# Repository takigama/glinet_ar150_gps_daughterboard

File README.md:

## Update - 2020, Mar 9

I've been running my little guys for 3 years now. I have two in outdoor cases
being powered over ethernet and they have yet to skip a beat, which is suprising.
As some of you may know, Australia (especially NSW) has been going through
some hard times this summer. First it was an amazing heatwave followed by fire
Then it was floods and intense rain. They endured both. Going up against two
RPI's (both RPI's died in the heat), thats doing pretty well.

I've now added a 2020 firmware release which is based on 19.07.2. This time
i've included all the packages as well and made as many modules as would
compile. If you do need any extra modules, they should now already be available

I've not chaned the firmware to point here for packages however, so you need
to grab them manually.

I also plan on publishing a build guide for the external cases, hopefully
some time soon.

## What be it?

Simple daughter board for the AR150 from GL.inet using the Quectel L80 GPS or
the MTK3339 GPS (there are boards for either)

... and its AWESOME!!!!

... and NOW with added linuxptp AND LEDE support!!!!!

note that it doesnt come configured with much, so most of the daemons included
(ntp, chrony, etc) start up automatically with defaults, you want to change
that

## Why?

meh, why not?

Seriously though, some time ago I used the predessesor of the AR150 and the
uBlox Neo 6m GPS receiver to build a NTP with GPS and PPS for high accuracy
timing. [See here](http://pjrlost.blogspot.com.au/2015/09/ar9331-pps-gps-ntp-awesome.html)
I had to write some code to enable PPS interupt based processing on the AR9331
family (thanks to some code that already supported GPIO's with interrupts)
and was fairly impressed with the results. At home its the prefered clock
source, going up against a RPI1, RPI2 and a Wyse terminal with a serial port
which runs an AMD geode cpu.

Sadly its hard to get the Neo uBlox 6M in an SMD format, but I stumbled onto
the Quectel L80 chip, which is easy to aquire and even smaller than the uBlox. The AR150
has different GPIO pins to the original GL.inet router I had in my previous
project (which is still actually running at home and still out-performing
most other GPS/PPS's i've built).

A number of projects do use the AR9331 as a GPS/PPS/NTP clock, but this was
the first one that I know of that implemented by the gpio interrupt mechanism
(which is more accurate and more efficient).

## How?

Well, first go print a board at oshpark [here](https://oshpark.com/shared_projects/Jt3Wxv2q)
and then go get a Quectel L80 chip (just the chip, no board), a couple of leds
a small mosfet (dont really need it to be honest) and a few resistors and lastly
of course a AR150.

Solder it all together, then sit back and wait for me to port my code on the
blog to the AR150 (only have to change the PPS pin from 13 to 14), or compile
the code yourself and figure that bit out.

Also, when i started this, i was thinking along the lines of the PoE version
of the AR150 (so the AR150 can sit outside in a silicon case with the GPS poking
upward thru the top - i'll post pic's when I build it)

Dont let the SMD scare you, plenty of youtubes up for how to hand solder or heat
gun solder this thing. I use a head gun for everything except the GPS module. I
use a soldering iron for the GPS module.

## BOM

1) 1 x L80 GPS Module or MTK3339 Module
2) 1 x Mosfet (BSS138 or similar) - optional, allows GPS to be power cycled by board
3) 3 x 200ohm 0805 SMD resistors
4) 1 x 2x5 90 degree angled pin header
5) 3 x 0805 leds (colour is up to you)

## GPIO's

So in the project, its using two GPIO's. One is used to turn the GPS itself on
and off. The other is used for the PPS interrupt. GPIO 17 is the power switch
GPIO 14 will be the PPS pin.

## Updates

3/Mar/2018 - There are now two firmwares sitting in the firmware directory. This
update moves my repo from its very-alpha state to something I now consider to be
relatively tested and working fairly stable and as such is now considered beta!

The baords have both beeen tested with fairly good success so far. I would
slightly recommend the L80 GPS over the MTK3339 GPS module as it seems more
sensative and less jittery.

Heres some Pics for you:

L80:

MTK3339:

Theres no alot to distinguish between the two except they have different footprints
on the GPS module

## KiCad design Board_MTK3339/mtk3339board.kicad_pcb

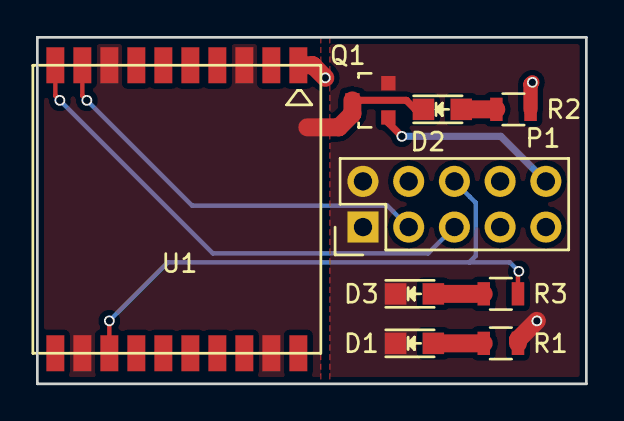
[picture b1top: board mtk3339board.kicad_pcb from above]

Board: 2 copper layers, 30.5 x 19.2 mm, 9 parts (0 on the bottom side), 10 nets.

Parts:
D1, D2, D3: LED; LED_0805
P1: CONN_02X05; Pin_Header_Straight_2x05
Q1: BSS138; SOT-23
R1, R2, R3: 300; R_0805
U1: MTK3339

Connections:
+3V3: P1.9, R1.1, R2.1, U1.1
GND: D1.1, D3.1, P1.1, P1.2, Q1.2
GP_14: P1.6, R3.1, U1.13
GP_17: P1.10, Q1.1
GP_GND: D2.1, Q1.3, U1.3, U1.8, U1.12, U1.19
unnamed: D1.2, R1.2
unnamed: D2.2, R2.2
unnamed: D3.2, R3.2
RX: P1.3, U1.9
TX: P1.5, U1.10

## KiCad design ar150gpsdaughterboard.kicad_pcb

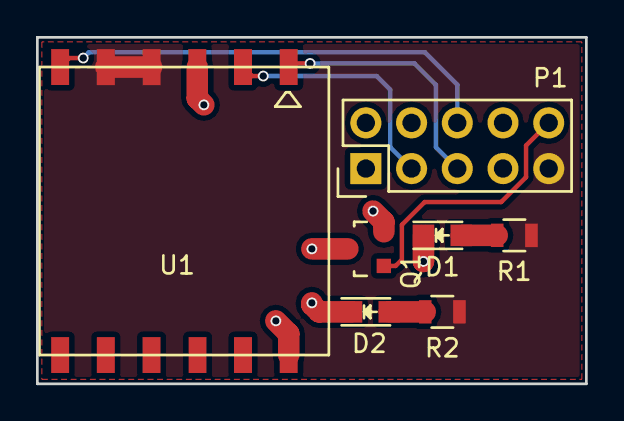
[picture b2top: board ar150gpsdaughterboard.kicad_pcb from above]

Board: 2 copper layers, 30.5 x 19.2 mm, 7 parts (0 on the bottom side), 9 nets.

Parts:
D1, D2: LED; LED_0805
P1: CONN_02X05; Pin_Header_Straight_2x05
Q1: BSS138; SOT-23
R1, R2: R; R_0805
U1: QUECTEL-L80

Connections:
+3V3: P1.9, R1.1, R2.1, U1.4, U1.5
GND: D1.1, P1.1, P1.2, Q1.2
GP_14: P1.6, U1.6
GP_17: P1.10, Q1.1
GP_GND: D2.1, Q1.3, U1.3, U1.12
unnamed: D1.2, R1.2
unnamed: D2.2, R2.2
RX: P1.3, U1.2
TX: P1.5, U1.1

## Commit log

2017-05-10 GL.inet AR150 GPS Daughter board Project
2017-05-10 added a readme
2017-06-08 new pinout
2017-06-08 Updated board layout - new L80 footprint, better location of pins
2017-06-08 updated oshpark link in readme
2017-06-09 updated pinout of the ar150 pin header
2017-06-11 new board with a pps line indicator
2017-06-11 firmware and build guide - very succinct
2017-06-11 added a command to output pps at all times
2017-06-11 some new additions
2017-06-11 reloaction for an mtk based board
2017-06-11 complete MTK board
2017-06-12 updated baord for MTK3339 - should sit more correclty now
2017-06-12 updated baord for L80 - should sit more correclty now
2017-11-22 Added photo's of built boards
2018-02-06 added ptp and ethtool to firmware
2018-02-18 added complete hack to support lede, proper linuxptp support
2018-02-18 new lede firmwre - extra packages
2018-02-18 upddated readme
2018-02-19 patch update aftere much backtracing
2018-02-19 now with kernel that ACTUALLY works
2018-02-19 new config
2018-02-20 Now with less hackery
2018-02-20 upated readme
2018-03-03 new firmware - now in beta
2018-03-03 updated readme and firmwares - now start ptp4l
2018-03-03 added 3d printed case
2018-03-14 Changed the cablein gland so it can accomodate a rj45 withtot having to seal it in
2020-03-05 Time to build ye once more
2020-03-05 quick run build guide
2020-03-05 setup some structure
2020-03-05 added current config
2020-03-08 new build based on 19.07.2 - added packages
